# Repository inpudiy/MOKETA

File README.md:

# MOKETA

MOKETA is an open-source unibody 42-key wireless keyboard with MX switches, per-key LEDs, status indicators, a 3D-printed box-mount case, and a hot-swappable Pro Micro–compatible controller.

[Build Guide](BUILD.md) | [ZMK Firmware](https://github.com/inpudiy/zmk-MOKETA)

## Features

- Unibody form factor with a 15 degree angle between halves
- 42-key column-staggered layout with MX switches
- 3D-printed box mount case
- 4 status LEDs inspired by the Aroum project
- Per-switch SK6812MINI-E LEDs
- Pro Micro compatible microcontroller with hot-swap (nice!nano, SuperMini NRF52840, Mikoto, or another)
- Optimized for wireless use: hardware power switch, reset button, battery solder pads, and ZMK firmware

## PCB Image

## Bill of materials

| Component                                                    | Qty/Pin |
| ------------------------------------------------------------ | ------- |
| Pro Micro board: Super Mini nRF52840 / nice!nano             | 1       |
| MSK12C02 Slide Switch                                        | 1       |
| TS342A2P                                                     | 1       |
| 50mm Industrial H62 brass wire 0.5mm thickness               | 1       |
| 0805 Led                                                     | 4       |
| 0805 Resitor                                                 | 4       |
| Silicone bumpers                                             | 6       |
| Machine Pin Header Female                                    | 24      |
| PG1511 hot-swap socket                                       | 42      |
| Diode 1N4148W (SOD-123)                                      | 42      |
| MX switches                                                  | 42      |
| SK6812MINI-E                                                 | 42      |
| Silicone (Optional)

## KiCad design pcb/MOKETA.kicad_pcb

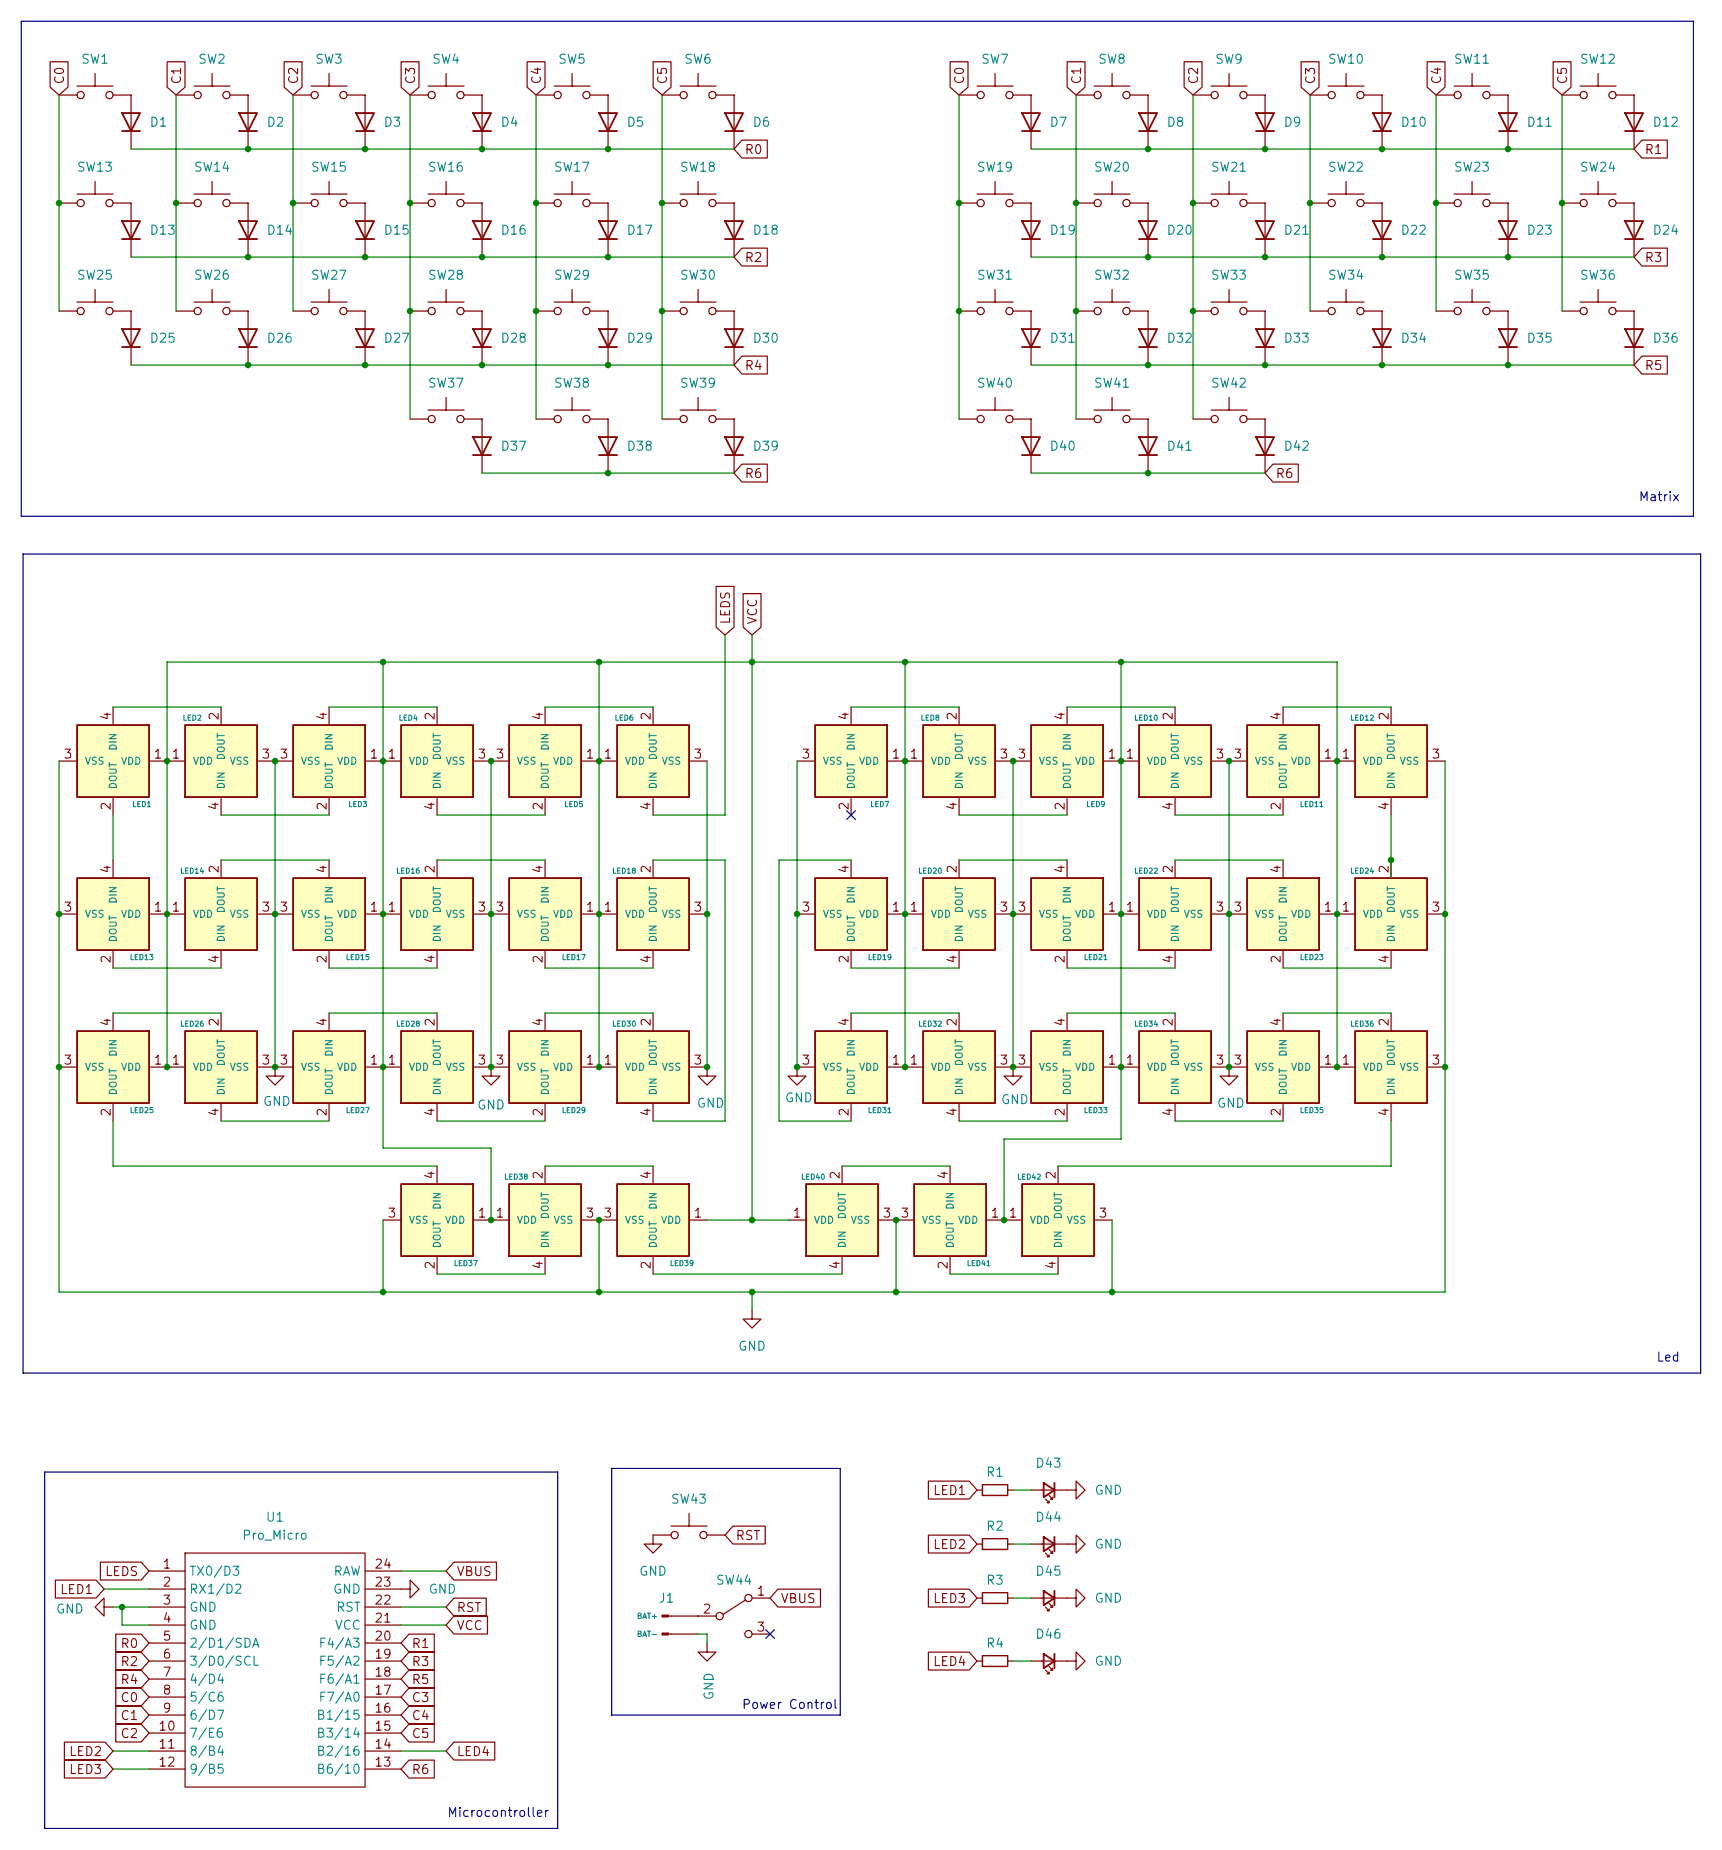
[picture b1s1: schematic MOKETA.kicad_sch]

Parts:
D1, D2, D3, D4, D5, D6, D7, D8, D9, D10, D11, D12, D13, D14, D15, D16, D17, D18, D19, D20, D21, D22, D23, D24, D25, D26, D27, D28, D29, D30, D31, D32, D33, D34, D35, D36, D37, D38, D39, D40, D41, D42: Diode; D_SOD-123
D43, D44, D45, D46: LED_1206
J1: J_BATTERY
LED1, LED2, LED3, LED4, LED5, LED6, LED7, LED8, LED9, LED10, LED11, LED12, LED13, LED14, LED15, LED16, LED17, LED18, LED19, LED20, LED21, LED22, LED23, LED24, LED25, LED26, LED27, LED28, LED29, LED30, LED31, LED32, LED33, LED34, LED35, LED36, LED37, LED38, LED39, LED40, LED41, LED42: YS-SK6812MINI-E
R1, R2, R3, R4: R_1206_3216
SW1, SW2, SW3, SW4, SW5, SW6, SW7, SW8, SW9, SW10, SW11, SW12, SW13, SW14, SW15, SW16, SW17, SW18, SW19, SW20, SW21, SW22, SW23, SW24, SW25, SW26, SW27, SW28, SW29, SW30, SW31, SW32, SW33, SW34, SW35, SW36, SW37, SW38, SW39, SW40, SW41, SW42: SW_PUSH
SW43: Reset; SW_TACT
SW44: MSK-12C02
U1: Pro_Micro; U_PRO_MICRO

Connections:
C0: SW1.1, SW7.1, SW13.1, SW19.1, SW25.1, SW31.1, SW40.1, U1.8 (5/C6)
C1: SW2.1, SW8.1, SW14.1, SW20.1, SW26.1, SW32.1, SW41.1, U1.9 (6/D7)
C2: SW3.1, SW9.1, SW15.1, SW21.1, SW27.1, SW33.1, SW42.1, U1.10 (7/E6)
C3: SW4.1, SW10.1, SW16.1, SW22.1, SW28.1, SW34.1, SW37.1, U1.17 (F7/A0)
C4: SW5.1, SW11.1, SW17.1, SW23.1, SW29.1, SW35.1, SW38.1, U1.16 (B1/15)
C5: SW6.1, SW12.1, SW18.1, SW24.1, SW30.1, SW36.1, SW39.1, U1.15 (B3/14)
GND: D43.1 (K), D44.1 (K), D45.1 (K), D46.1 (K), J1.2 (BAT-), LED1.3 (VSS), LED2.3 (VSS), LED3.3 (VSS), LED4.3 (VSS), LED5.3 (VSS), LED6.3 (VSS), LED7.3 (VSS), LED8.3 (VSS), LED9.3 (VSS), LED10.3 (VSS), LED11.3 (VSS), LED12.3 (VSS), LED13.3 (VSS), LED14.3 (VSS), LED15.3 (VSS), LED16.3 (VSS), LED17.3 (VSS), LED18.3 (VSS), LED19.3 (VSS), LED20.3 (VSS), LED21.3 (VSS), LED22.3 (VSS), LED23.3 (VSS), LED24.3 (VSS), LED25.3 (VSS), LED26.3 (VSS), LED27.3 (VSS), LED28.3 (VSS), LED29.3 (VSS), LED30.3 (VSS), LED31.3 (VSS), LED32.3 (VSS), LED33.3 (VSS), LED34.3 (VSS), LED35.3 (VSS), LED36.3 (VSS), LED37.3 (VSS), LED38.3 (VSS), LED39.3 (VSS), LED40.3 (VSS), LED41.3 (VSS), LED42.3 (VSS), SW43.1, U1.3 (GND), U1.4 (GND), U1.23 (GND)
LED1: R1.1, U1.2 (RX1/D2)
LED2: R2.1, U1.11 (8/B4)
LED3: R3.1, U1.12 (9/B5)
LED4: R4.1, U1.14 (B2/16)
LEDS: LED6.4 (DIN), U1.1 (TX0/D3)
unnamed: D1.2 (A), SW1.2
unnamed: D2.2 (A), SW2.2
unnamed: D3.2 (A), SW3.2
unnamed: D4.2 (A), SW4.2
unnamed: D5.2 (A), SW5.2
unnamed: D6.2 (A), SW6.2
unnamed: D7.2 (A), SW7.2
unnamed: D8.2 (A), SW8.2
unnamed: D9.2 (A), SW9.2
unnamed: D10.2 (A), SW10.2
unnamed: D11.2 (A), SW11.2
unnamed: D12.2 (A), SW12.2
unnamed: D13.2 (A), SW13.2
unnamed: D14.2 (A), SW14.2
unnamed: D15.2 (A), SW15.2
unnamed: D16.2 (A), SW16.2
unnamed: D17.2 (A), SW17.2
unnamed: D18.2 (A), SW18.2
unnamed: D19.2 (A), SW19.2
unnamed: D20.2 (A), SW20.2
unnamed: D21.2 (A), SW21.2
unnamed: D22.2 (A), SW22.2
unnamed: D23.2 (A), SW23.2
unnamed: D24.2 (A), SW24.2
unnamed: D25.2 (A), SW25.2
unnamed: D26.2 (A), SW26.2
unnamed: D27.2 (A), SW27.2
unnamed: D28.2 (A), SW28.2
unnamed: D29.2 (A), SW29.2
unnamed: D30.2 (A), SW30.2
unnamed: D31.2 (A), SW31.2
unnamed: D32.2 (A), SW32.2
unnamed: D33.2 (A), SW33.2
unnamed: D34.2 (A), SW34.2
unnamed: D35.2 (A), SW35.2
unnamed: D36.2 (A), SW36.2
unnamed: D37.2 (A), SW37.2
unnamed: D38.2 (A), SW38.2
unnamed: D39.2 (A), SW39.2
unnamed: D40.2 (A), SW40.2
unnamed: D41.2 (A), SW41.2
unnamed: D42.2 (A), SW42.2
unnamed: D43.2 (A), R1.2
unnamed: D44.2 (A), R2.2
unnamed: D45.2 (A), R3.2
unnamed: D46.2 (A), R4.2
unnamed: J1.1 (BAT+), SW44.2 (B)
unnamed: LED1.4 (DIN), LED2.2 (DOUT)
unnamed: LED1.2 (DOUT), LED13.4 (DIN)
unnamed: LED2.4 (DIN), LED3.2 (DOUT)
unnamed: LED3.4 (DIN), LED4.2 (DOUT)
unnamed: LED4.4 (DIN), LED5.2 (DOUT)
unnamed: LED5.4 (DIN), LED6.2 (DOUT)
unnamed: LED7.4 (DIN), LED8.2 (DOUT)
unnamed: LED8.4 (DIN), LED9.2 (DOUT)
unnamed: LED10.4 (DIN), LED11.2 (DOUT)
unnamed: LED9.4 (DIN), LED10.2 (DOUT)
unnamed: LED11.4 (DIN), LED12.2 (DOUT)
unnamed: LED12.4 (DIN), LED24.2 (DOUT)
unnamed: LED13.2 (DOUT), LED14.4 (DIN)
unnamed: LED14.2 (DOUT), LED15.4 (DIN)
unnamed: LED15.2 (DOUT), LED16.4 (DIN)
unnamed: LED16.2 (DOUT), LED17.4 (DIN)
unnamed: LED17.2 (DOUT), LED18.4 (DIN)
unnamed: LED18.2 (DOUT), LED30.4 (DIN)
unnamed: LED19.4 (DIN), LED31.2 (DOUT)
unnamed: LED19.2 (DOUT), LED20.4 (DIN)
unnamed: LED20.2 (DOUT), LED21.4 (DIN)
unnamed: LED21.2 (DOUT), LED22.4 (DIN)
unnamed: LED22.2 (DOUT), LED23.4 (DIN)
unnamed: LED23.2 (DOUT), LED24.4 (DIN)
unnamed: LED25.4 (DIN), LED26.2 (DOUT)
unnamed: LED25.2 (DOUT), LED37.4 (DIN)
unnamed: LED26.4 (DIN), LED27.2 (DOUT)
unnamed: LED27.4 (DIN), LED28.2 (DOUT)
unnamed: LED28.4 (DIN), LED29.2 (DOUT)
unnamed: LED29.4 (DIN), LED30.2 (DOUT)
unnamed: LED31.4 (DIN), LED32.2 (DOUT)
unnamed: LED32.4 (DIN), LED33.2 (DOUT)
unnamed: LED33.4 (DIN), LED34.2 (DOUT)
unnamed: LED34.4 (DIN), LED35.2 (DOUT)
unnamed: LED35.4 (DIN), LED36.2 (DOUT)
unnamed: LED36.4 (DIN), LED42.2 (DOUT)
unnamed: LED37.2 (DOUT), LED38.4 (DIN)
unnamed: LED38.2 (DOUT), LED39.4 (DIN)
unnamed: LED39.2 (DOUT), LED40.4 (DIN)
unnamed: LED40.2 (DOUT), LED41.4 (DIN)
unnamed: LED41.2 (DOUT), LED42.4 (DIN)
R0: D1.1 (K), D2.1 (K), D3.1 (K), D4.1 (K), D5.1 (K), D6.1 (K), U1.5 (2/D1/SDA)
R1: D7.1 (K), D8.1 (K), D9.1 (K), D10.1 (K), D11.1 (K), D12.1 (K), U1.20 (F4/A3)
R2: D13.1 (K), D14.1 (K), D15.1 (K), D16.1 (K), D17.1 (K), D18.1 (K), U1.6 (3/D0/SCL)
R3: D19.1 (K), D20.1 (K), D21.1 (K), D22.1 (K), D23.1 (K), D24.1 (K), U1.19 (F5/A2)
R4: D25.1 (K), D26.1 (K), D27.1 (K), D28.1 (K), D29.1 (K), D30.1 (K), U1.7 (4/D4)
R5: D31.1 (K), D32.1 (K), D33.1 (K), D34.1 (K), D35.1 (K), D36.1 (K), U1.18 (F6/A1)
R6: D37.1 (K), D38.1 (K), D39.1 (K), D40.1 (K), D41.1 (K), D42.1 (K), U1.13 (B6/10)
RST: SW43.2, U1.22 (RST)
VBUS: SW44.1 (A), U1.24 (RAW)
VCC: LED1.1 (VDD), LED2.1 (VDD), LED3.1 (VDD), LED4.1 (VDD), LED5.1 (VDD), LED6.1 (VDD), LED7.1 (VDD), LED8.1 (VDD), LED9.1 (VDD), LED10.1 (VDD), LED11.1 (VDD), LED12.1 (VDD), LED13.1 (VDD), LED14.1 (VDD), LED15.1 (VDD), LED16.1 (VDD), LED17.1 (VDD), LED18.1 (VDD), LED19.1 (VDD), LED20.1 (VDD), LED21.1 (VDD), LED22.1 (VDD), LED23.1 (VDD), LED24.1 (VDD), LED25.1 (VDD), LED26.1 (VDD), LED27.1 (VDD), LED28.1 (VDD), LED29.1 (VDD), LED30.1 (VDD), LED31.1 (VDD), LED32.1 (VDD), LED33.1 (VDD), LED34.1 (VDD), LED35.1 (VDD), LED36.1 (VDD), LED37.1 (VDD), LED38.1 (VDD), LED39.1 (VDD), LED40.1 (VDD), LED41.1 (VDD), LED42.1 (VDD), U1.21 (VCC)

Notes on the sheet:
Matrix
Power Control
Microcontroller
Led

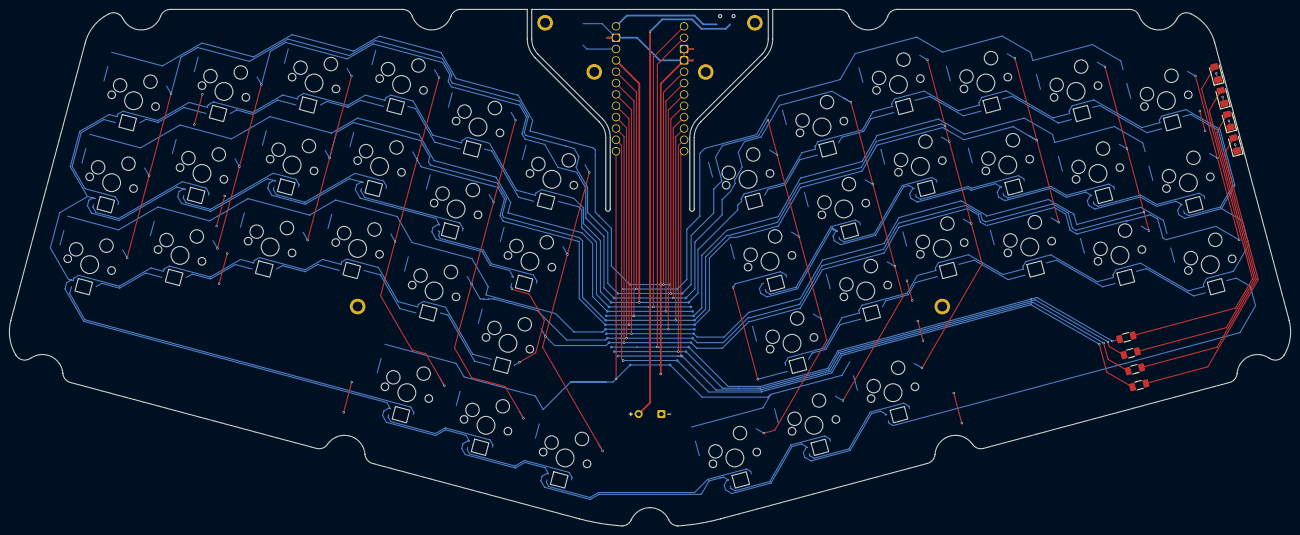
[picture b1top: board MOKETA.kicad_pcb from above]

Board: 2 copper layers, 286.8 x 115.6 mm, 144 parts (0 on the bottom side), 110 nets.

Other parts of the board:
MH: Untitled; M2 Hole
MH#2, MH#3, MH#4, MH#5, MH#6: Untitled; M2 Hole

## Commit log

2025-07-18 add switches
2025-07-20 New MOKETA otuline
2025-07-28 aling col and row
2025-07-28 add footrpint
2025-07-28 fix LED footprint
2025-07-29 update footprint
2025-07-30 clear repo
2025-07-30 add RGB to scheme
2025-07-30 some fix
2025-07-30 fix led
2025-07-30 update LED footprint
2025-07-30 update pad
2025-07-30 add outline
2025-08-01 Remove cache that shouldnt be tracked
2025-08-01 Untrack kbplacer.log
2025-08-02 Basic routing
2025-08-06 change footrpint
2025-08-12 Doter pcb base cut
2025-08-12 update footptint
2025-08-13 Basic routing on almost whole board
2025-08-18 update footpint
2025-08-18 Extended board, 38 mm between thumbs
2025-08-19 Connector on doter rotated 180 degree
2025-08-21 add hole
2025-08-22 No separate doter, flex PCB instead
2025-08-22 Add another 2 holes on controller zone
2025-08-22 pre release upload
2025-08-22 Fixes after DRC checks
2025-08-22 Cuprum paint
2025-08-22 Slightly rerouted visual around moketa planet
2025-08-24 Hole pads placement fix
2025-08-24 Minor fixes
2025-08-24 last fix
2025-08-24 Tune for fabrication
2025-08-24 fix silc
2025-08-24 clear lib
2025-08-24 fix brandmark
2025-08-25 Fix power lines from power switch
2025-08-25 Move micro via near power switch
2025-08-26 generate gerber
2025-09-09 update model
2025-11-02 add README.md
2025-11-02 update reamde
2025-12-02 Case TE files added
2025-12-02 Added bottom variations for silicone pads 8mm and 10mm
2025-12-14 add BUILD GUIDE
